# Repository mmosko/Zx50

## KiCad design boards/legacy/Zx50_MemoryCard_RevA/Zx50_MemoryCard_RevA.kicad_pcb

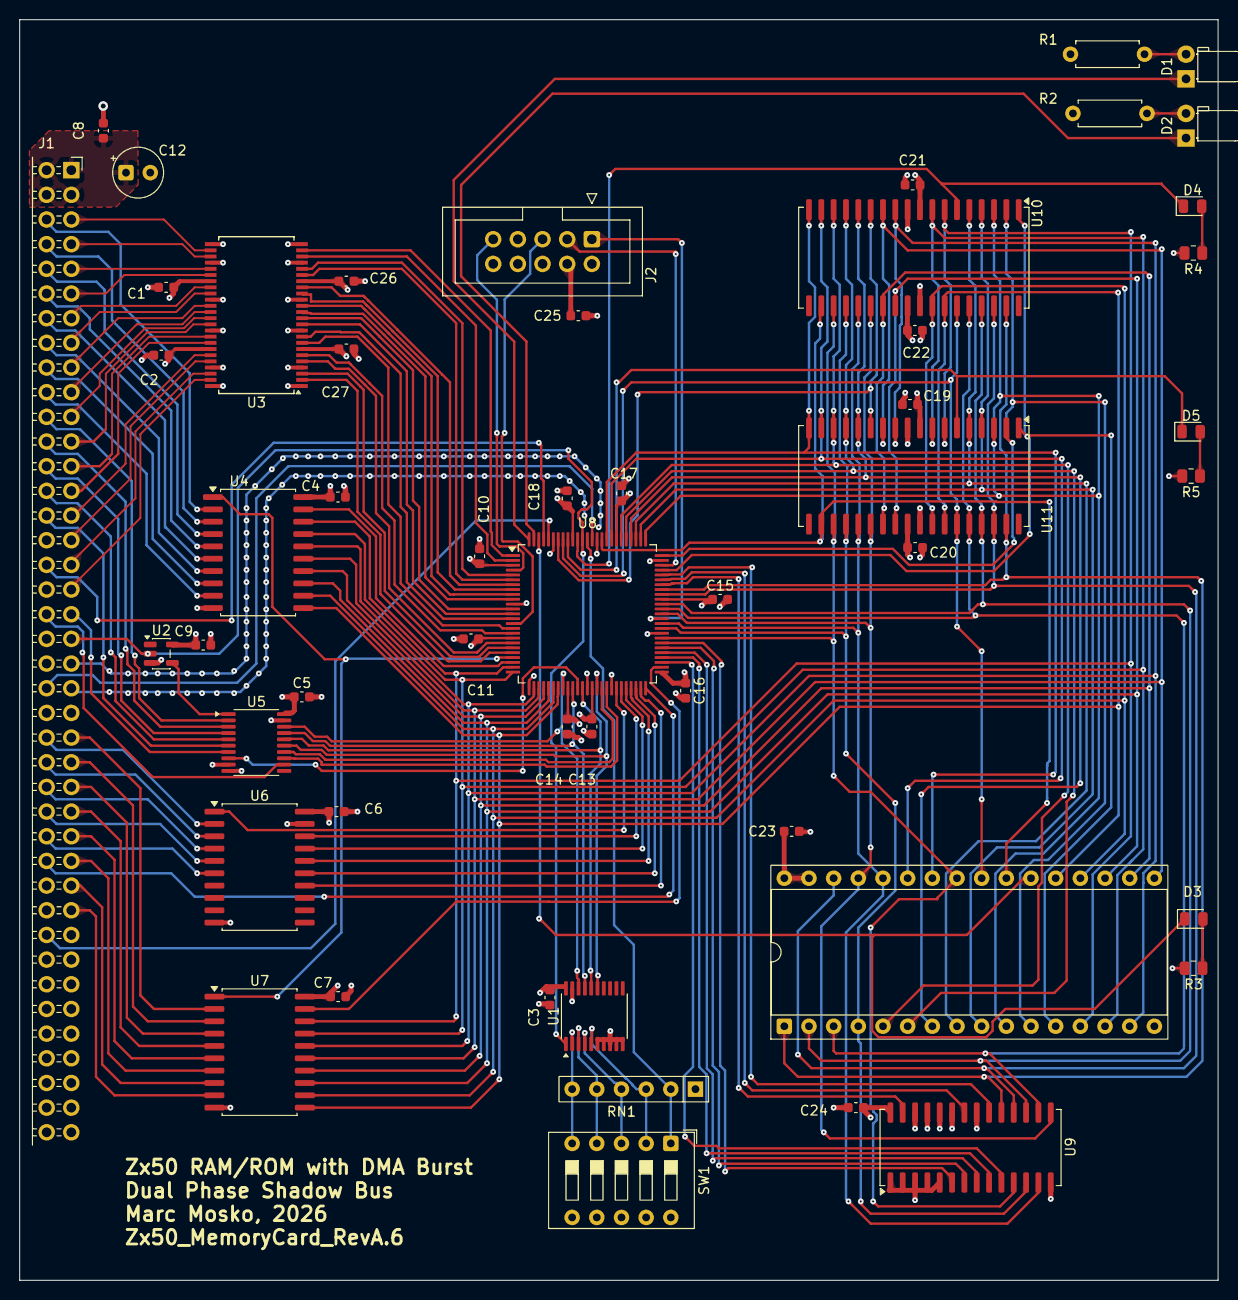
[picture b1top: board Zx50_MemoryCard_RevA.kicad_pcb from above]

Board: 4 copper layers, 123.4 x 129.8 mm, 53 parts (0 on the bottom side), 140 nets.

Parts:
C1, C2, C3, C4, C5, C6, C7, C8, C9, C26, C27: 0.1uF; C_0603_1608Metric
C10, C11, C13, C14, C15, C16, C17, C18, C19, C20, C21, C22, C23, C24, C25: .1uF; C_0603_1608Metric
C12: 10uF; CP_Radial_Tantal_D5.0mm_P2.50mm
D1, D2: LED; LED_D3.0mm_Horizontal_O1.27mm_Z2.0mm
D3: YLW; LED_0805_2012Metric
D4, D5: BLUE; LED_0805_2012Metric
J1: Zx50_EdgeConnector; PinSocket_2x40_P2.54mm_Horizontal_Edge
J2: JTAG; IDC-Header_2x05_P2.54mm_Vertical
R1, R2: 470; R_Axial_DIN0207_L6.3mm_D2.5mm_P7.62mm_Horizontal
R3, R4, R5: 470; R_0805_2012Metric
RN1: 10K; R_Array_SIP6
SW1: SW_DIP_x05; SW_DIP_SPSTx05_Slide_9.78x14.88mm_W7.62mm_P2.54mm
U1, U5: SN74ABT541BN; TSSOP-20_4.4x6.5mm_P0.65mm
U2: 74AHCT1G04; SOT-23-5
U3: SN74ABT16244ADL; SSOP-48_7.5x15.9mm_P0.635mm
U4, U6, U7: 74ABT245; SOIC-20W_7.5x12.8mm_P1.27mm
U8: ATF1508AS-10AU100; TQFP-100_14x14mm_P0.5mm
U9: IS61C256AL-12JLI; SOJ-28_7.62x18.415mm_P1.27mm
U10, U11: CY7C1049GN; SOJ-36_10.16x23.495mm_P1.27mm
U12: SST39SF040; DIP-32_W15.24mm_Socket

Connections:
+5V: C1.1, C2.1, C3.1, C4.1, C5.1, C6.1, C7.1, C8.1, C9.1, C10.1, C11.1, C12.1, C13.1, C14.1, C15.1, C16.1, C17.1, C18.1, C19.1, C20.1, C21.1, C22.1, C23.1, C24.1, C25.1, C26.1, C27.1, J1.1 (+5V), J1.2 (+5V), J1.3 (+5V), J1.4 (+5V), J2.4, R1.1, R2.1, R3.2, R4.2, R5.2, RN1.1 (common), U1.20 (VCC), U2.5 (VCC), U3.7 (VCC), U3.18 (VCC), U3.31 (VCC), U3.42 (VCC), U4.20 (VCC), U5.20 (VCC), U6.20 (VCC), U7.20 (VCC), U8.3 (VCCIO), U8.18 (VCCIO), U8.34 (VCCIO), U8.39 (VCCINT), U8.51 (VCCIO), U8.66 (VCCIO), U8.82 (VCCIO), U8.91 (VCCINT), U9.28 (VCC), U10.9 (VCC), U10.27 (VCC), U11.9 (VCC), U11.27 (VCC), U12.31 (PGM), U12.32 (VCC)
/A0: J1.5 (A0), U3.26 (4A4)
/A1: J1.7 (A1), U3.27 (4A3)
/A2: J1.9 (A2), U3.29 (4A2)
/A3: J1.11 (A3), U3.30 (4A1)
/A4: J1.13 (A4), U3.32 (3A4)
/A5: J1.15 (A5), U3.33 (3A3)
/A6: J1.17 (A6), U3.35 (3A2)
/A7: J1.19 (A7), U3.36 (3A1)
/A8: J1.21 (A8), U3.37 (2A4)
/A9: J1.23 (A9), U3.38 (2A3)
/A10: J1.25 (A10), U3.40 (2A2)
/A11: J1.27 (A11), U3.41 (2A1)
/A12: J1.29 (A12), U3.43 (1A4)
/A13: J1.31 (A13), U3.44 (1A3)
/A14: J1.33 (A14), U3.46 (1A2)
/A15: J1.35 (A15), U3.47 (1A1)
/B.A0: U3.23 (4Y4), U8.1 (Z80_A0)
/B.A1: U3.22 (4Y3), U8.2 (Z80_A1)
/B.A2: U3.20 (4Y2), U8.5 (Z80_A2)
/B.A3: U3.19 (4Y1), U8.6 (Z80_A3)
/B.A4: U3.17 (3Y4), U8.7 (Z80_A4)
/B.A5: U3.16 (3Y3), U8.8 (Z80_A5)
/B.A6: U3.14 (3Y2), U8.9 (Z80_A6)
/B.A7: U3.13 (3Y1), U8.10 (Z80_A7)
/B.A8: U3.12 (2Y4), U8.12 (Z80_A8)
/B.A9: U3.11 (2Y3), U8.13 (Z80_A9)
/B.A10: U3.9 (2Y2), U8.14 (Z80_A10)
/B.A11: U3.8 (2Y1), U8.16 (Z80_A11)
/B.A12: U3.6 (1Y4), U8.17 (Z80_A12)
/B.A13: U3.5 (1Y3), U8.19 (Z80_A13)
/B.A14: U3.3 (1Y2), U8.20 (Z80_A14)
/B.A15: U3.2 (1Y1), U8.21 (Z80_A15)
/B.D0: U4.18 (B1), U7.18 (B1), U8.24 (L_D0), U10.7 (I/O0), U11.7 (I/O0), U12.13 (D0)
/B.D1: U4.17 (B2), U7.17 (B2), U8.25 (L_D1), U10.8 (I/O1), U11.8 (I/O1), U12.14 (D1)
/B.D2: U4.16 (B3), U7.16 (B3), U8.27 (L_D2), U10.11 (I/O2), U11.11 (I/O2), U12.15 (D2)
/B.D3: U4.15 (B4), U7.15 (B4), U8.28 (L_D3), U10.12 (I/O3), U11.12 (I/O3), U12.17 (D3)
/B.D4: U4.14 (B5), U7.14 (B5), U8.29 (L_D4), U10.25 (I/O4), U11.25 (I/O4), U12.18 (D4)
/B.D5: U4.13 (B6), U7.13 (B6), U8.30 (L_D5), U10.26 (I/O5), U11.26 (I/O5), U12.19 (D5)
/B.D6: U4.12 (B7), U7.12 (B7), U8.31 (L_D6), U10.29 (I/O6), U11.29 (I/O6), U12.20 (D6)
/B.D7: U4.11 (B8), U7.11 (B8), U8.32 (L_D7), U10.30 (I/O7), U11.30 (I/O7), U12.21 (D7)
/B.IEI: U5.13 (Y6), U8.42 (Z80_IEI)
/B.IEO: U5.8 (A7), U8.36 (Z80_IEO)
/B.SH_RW: U6.15 (B4), U8.48 (SH_RW_n)
/B.~IORQ~: U1.15 (Y4), U5.15 (Y4), U8.40 (Z80_IORQ_n)
/B.~M1~: U5.14 (Y5), U8.41 (Z80_M1_n)
/B.~MREQ~: U1.16 (Y3), U5.16 (Y3), U8.37 (Z80_MREQ_n)
/B.~RD~: U1.18 (Y1), U5.18 (Y1), U8.33 (Z80_RD_n)
/B.~SH_DONE~: U6.14 (B5), U8.49 (SH_DONE_n)
/B.~SH_EN~: U6.16 (B3), U8.47 (SH_EN_n)
/B.~SH_INC~: U6.17 (B2), U8.46 (SH_INC_n)
/B.~SH_STB~: U6.18 (B1), U8.45 (SH_STB_n)
/B.~WR~: U1.17 (Y2), U5.17 (Y2), U8.35 (Z80_WR_n)
/CPLD And Memory/ATL_A0: U8.53 (ATL_A0), U9.10 (A0)
/CPLD And Memory/ATL_A1: U8.54 (ATL_A1), U9.9 (A1)
/CPLD And Memory/ATL_A2: U8.55 (ATL_A2), U9.8 (A2)
/CPLD And Memory/ATL_A3: U8.56 (ATL_A3), U9.7 (A3)
/CPLD And Memory/ATL_A4: U8.57 (ATL_A4), U9.6 (A4)
/CPLD And Memory/ATL_D0: U8.58 (ATL_D0), U9.11 (I/O0), U10.21 (A11), U11.21 (A11), U12.25 (A11)
/CPLD And Memory/ATL_D1: U8.60 (ATL_D1), U9.12 (I/O1), U10.22 (A12), U11.22 (A12), U12.4 (A12)
/CPLD And Memory/ATL_D2: U8.61 (ATL_D2), U9.13 (I/O2), U10.23 (A13), U11.23 (A13), U12.28 (A13)
/CPLD And Memory/ATL_D3: U8.63 (ATL_D3), U9.15 (I/O3), U10.24 (A14), U11.24 (A14), U12.29 (A14)
/CPLD And Memory/ATL_D4: U8.64 (ATL_D4), U9.16 (I/O4), U10.32 (A15), U11.32 (A15), U12.3 (A15)
/CPLD And Memory/ATL_D5: U8.65 (ATL_D5), U9.17 (I/O5), U10.33 (A16), U11.33 (A16), U12.2 (A16)
/CPLD And Memory/ATL_D6: U8.67 (ATL_D6), U9.18 (I/O6), U10.34 (A17), U11.34 (A17), U12.30 (A17)
/CPLD And Memory/ATL_D7: U8.68 (ATL_D7), U9.19 (I/O7), U10.35 (A18), U11.35 (A18), U12.1 (A18)
/CPLD And Memory/L_A0: U8.72 (L_A0), U10.1 (A0), U11.1 (A0), U12.12 (A0)
/CPLD And Memory/L_A1: U8.75 (L_A1), U10.2 (A1), U11.2 (A1), U12.11 (A1)
/CPLD And Memory/L_A2: U8.76 (L_A2), U10.3 (A2), U11.3 (A2), U12.10 (A2)
/CPLD And Memory/L_A3: U8.77 (L_A3), U10.4 (A3), U11.4 (A3), U12.9 (A3)
/CPLD And Memory/L_A4: U8.78 (L_A4), U10.5 (A4), U11.5 (A4), U12.8 (A4)
/CPLD And Memory/L_A5: U8.79 (L_A5), U10.14 (A5), U11.14 (A5), U12.7 (A5)
/CPLD And Memory/L_A6: U8.80 (L_A6), U10.15 (A6), U11.15 (A6), U12.6 (A6)
/CPLD And Memory/L_A7: U8.81 (L_A7), U10.16 (A7), U11.16 (A7), U12.5 (A7)
/CPLD And Memory/L_A8: U8.83 (L_A8), U10.17 (A8), U11.17 (A8), U12.27 (A8)
/CPLD And Memory/L_A9: U8.84 (L_A9), U10.18 (A9), U11.18 (A9), U12.26 (A9)
/CPLD And Memory/L_A10: U8.85 (L_A10), U10.20 (A10), U11.20 (A10), U12.23 (A10)
/CPLD And Memory/TCLK: J2.1, U8.62 (TCK)
/CPLD And Memory/TDI: J2.9, U8.4 (TDI)
/CPLD And Memory/TDO: J2.3, U8.73 (TDO)
/CPLD And Memory/TMS: J2.5, U8.15 (TMS)
/CPLD And Memory/~ATL_CE~: U8.71 (ATL_CE_n), U9.20 (~CE)
/CPLD And Memory/~ATL_OE~: U8.70 (ATL_OE_n), U9.22 (~OE)
/CPLD And Memory/~ATL_WE~: U8.69 (ATL_WE_n), U9.27 (~WE)
/CPLD And Memory/~CE0~: D4.1 (K), U8.90 (RAM_CE0_n), U10.6 (~CE)
/CPLD And Memory/~CE1~: D5.1 (K), U8.92 (RAM_CE1_n), U11.6 (~CE)
/CPLD And Memory/~CE2~: D3.1 (K), U8.98 (ROM_C2), U12.22 (CE)
/CPLD And Memory/~OE~: U8.93 (RAM_OE_n), U10.31 (~OE), U11.31 (~OE), U12.24 (OE)
/CPLD And Memory/~WE~: U8.94 (RAM_WE_n), U10.13 (~WE), U11.13 (~WE)
/D_DIR: U4.1 (DIR), U7.1 (DIR), U8.22 (L_DIR)
/IEI: J1.37 (IEI), U5.7 (A6)
/IEO: J1.38 (IEO), U5.12 (Y7)
/MCLK: J1.44 (MCLK), U8.87 (MCLK)
/RESET: U2.4, U5.1 (*OE1)
/SD0: J1.47 (SD0), U7.2 (A1)
/SD1: J1.49 (SD1), U7.3 (A2)
/SD2: J1.51 (SD2), U7.4 (A3)
/SD3: J1.53 (SD3), U7.5 (A4)
/SD4: J1.55 (SD4), U7.6 (A5)
/SD5: J1.57 (SD5), U7.7 (A6)
/SD6: J1.59 (SD6), U7.8 (A7)
/SD7: J1.61 (SD7), U7.9 (A8)
/SH_C_DIR: U6.1 (DIR), U8.44 (SH_C_DIR)
/SH_RW: J1.54 (SRW), U6.5 (A4)
/~BOOT_EN~: RN1.2 (R1), SW1.1, U8.88 (BOOT_EN_n)
/~INT~: J1.64 (~INT~), U8.96 (Z80_INT_n)
/~IORQ~: J1.28 (~IORQ~), U5.5 (A4)
/~M1~: J1.30 (~M1~), U5.6 (A5)
/~MREQ~: J1.26 (~MREQ~), U5.4 (A3)
/~RD~: J1.22 (~RD~), U5.2 (A1)
/~RESET~: J1.39 (~RESET~), U1.1 (*OE1), U2.2, U8.89 (RESET_n)
/~SH_BUSY~: J1.58 (~S_BUSY~), U8.50 (SH_BUSY_n)
/~SH_DONE~: J1.56 (~S_DONE~), U6.6 (A5)
/~SH_D_OE~: U7.19 (*OE), U8.52 (SH_D_OE_n)
/~SH_EN~: J1.52 (~S_EN~), U6.4 (A3)
/~SH_INC~: J1.50 (~SINC~), U6.3 (A2)
/~SH_STB~: J1.48 (~SSTB~), U6.2 (A1)
/~WAIT~: J1.34 (~WAIT~), U8.97 (Z80_WAIT_n)
/~WR~: J1.24 (~WR~), U5.3 (A2)
/~Z80_D_OE~: U4.19 (*OE), U8.23 (Z80_DATA_OE_n)
GND: C1.2, C2.2, C3.2, C4.2, C5.2, C6.2, C7.2, C8.2, C9.2, C10.2, C11.2, C12.2, C13.2, C14.2, C15.2, C16.2, C17.2, C18.2, C19.2, C20.2, C21.2, C22.2, C23.2, C24.2, C25.2, C26.2, C27.2, J1.41 (GND), J1.43 (GND), J1.45 (GND), J1.46 (GND), J2.2, J2.10, SW1.6, SW1.7, SW1.8, SW1.9, SW1.10, U1.6 (A5), U1.7 (A6), U1.8 (A7), U1.9 (A8), U1.10 (GND), U1.19 (*OE2), U2.3 (GND), U3.1 (*1OE), U3.4 (GND), U3.10 (GND), U3.15 (GND), U3.21 (GND), U3.24 (*4OE), U3.25 (*3OE), U3.28 (GND), U3.34 (GND), U3.39 (GND), U3.45 (GND), U3.48 (*2OE), U4.10 (GND), U5.9 (A8), U5.10 (GND), U5.19 (*OE2), U6.10 (GND), U6.19 (*OE), U7.10 (GND), U8.11 (GND), U8.26 (GND), U8.38 (GND), U8.43 (GND), U8.59 (GND), U8.74 (GND), U8.86 (GND), U8.95 (GND), U9.1 (A14), U9.2 (A12), U9.3 (A7), U9.4 (A6), U9.5 (A5), U9.14 (GND), U9.21 (A10), U9.23 (A11), U9.24 (A9), U9.25 (A8), U9.26 (A13), U10.10 (GND), U10.28 (GND), U11.10 (GND), U11.28 (GND), U12.16 (GND)
unnamed: D1.2 (A), R1.2
unnamed: D1.1 (K), U8.100 (IO100)
unnamed: D2.2 (A), R2.2
unnamed: D2.1 (K), U8.99 (IO99)
unnamed: D3.2 (A), R3.1
unnamed: D4.2 (A), R4.1
unnamed: D5.2 (A), R5.1
unnamed: J1.6 (D0), U4.2 (A1)
unnamed: J1.8 (D1), U4.3 (A2)
unnamed: J1.10 (D2), U4.4 (A3)
unnamed: J1.12 (D3), U4.5 (A4)
unnamed: J1.14 (D4), U4.6 (A5)
unnamed: J1.16 (D5), U4.7 (A6)
unnamed: J1.18 (D6), U4.8 (A7)
unnamed: J1.20 (D7), U4.9 (A8)
unnamed: RN1.3 (R2), SW1.2, U1.5 (A4)
unnamed: RN1.4 (R3), SW1.3, U1.4 (A3)
unnamed: RN1.5 (R4), SW1.4, U1.3 (A2)
unnamed: RN1.6 (R5), SW1.5, U1.2 (A1)
